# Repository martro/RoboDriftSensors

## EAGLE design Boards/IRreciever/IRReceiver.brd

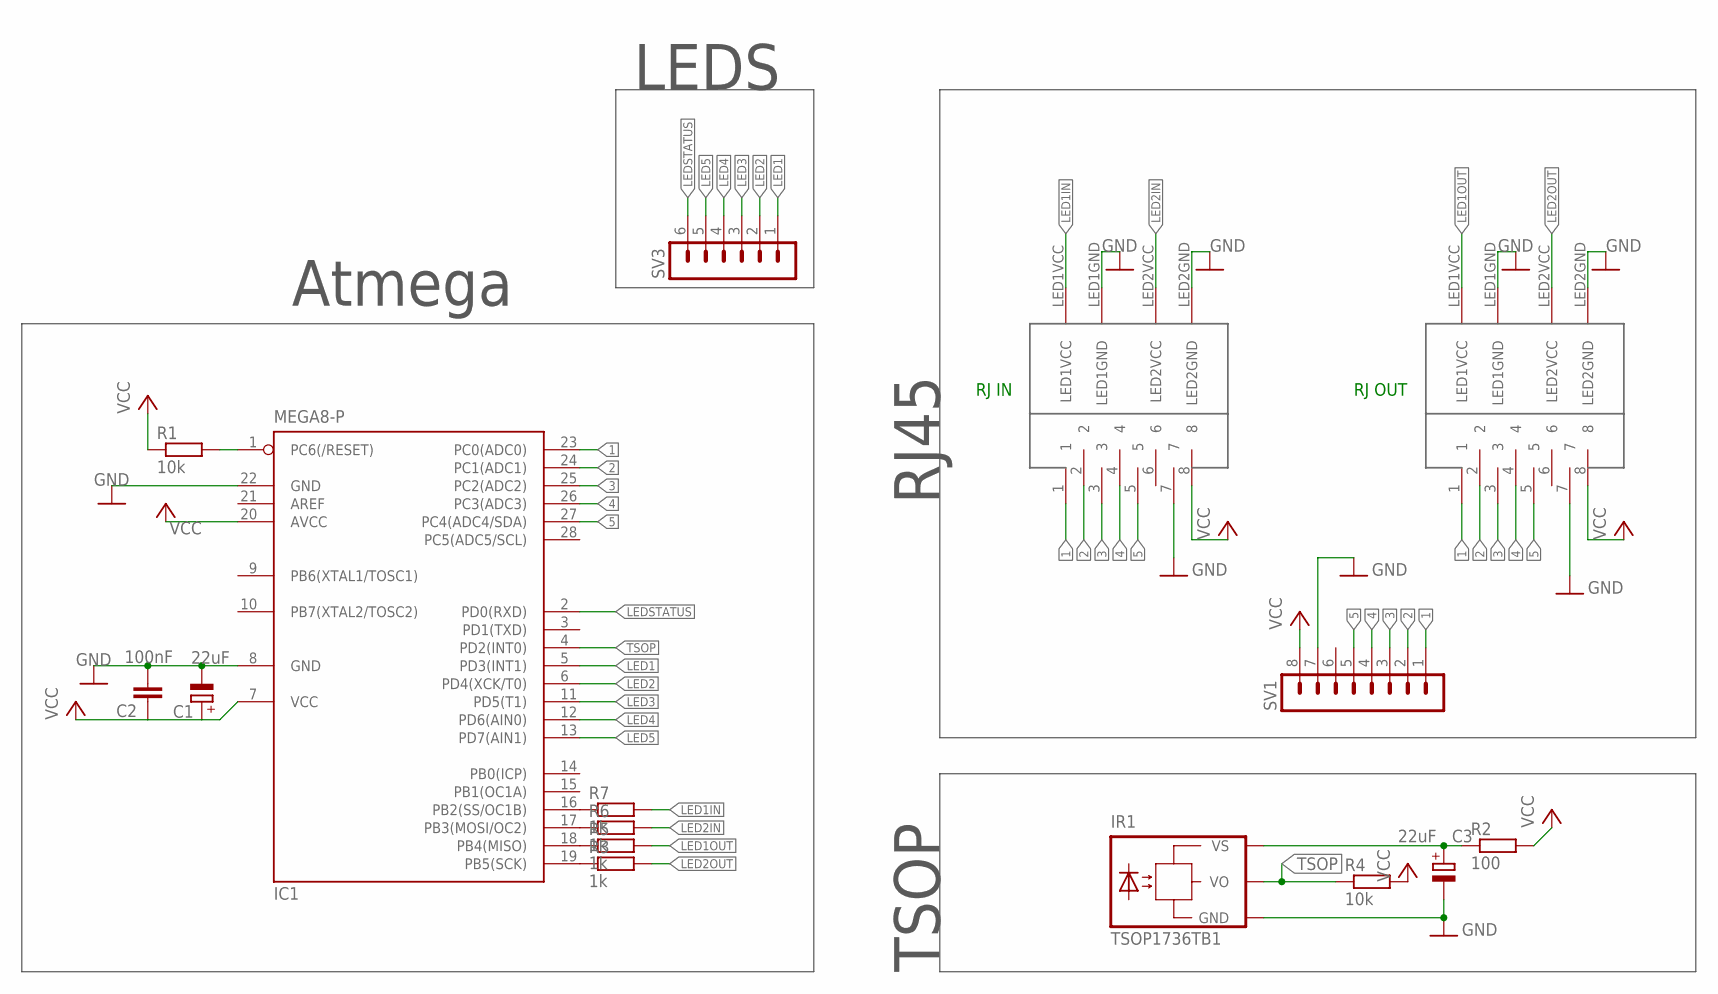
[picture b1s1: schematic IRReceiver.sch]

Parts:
C1, C3: 22uF; E5-5
C2: 100nF; C0805
IC1: MEGA8-P; DIL28-3
IR1: TSOP1736TB1; TSOP17_TB1
R1, R4: 10k; R0805
R2: 100; R0805
R3, R5, R6, R7: 1k; R0805
RJIN, RJIN1: 8P8CLED
SV1: MA08-1
SV3: MA06-1

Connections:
1: IC1.23 (PC0(ADC0)), RJIN.1, RJIN1.1, SV1.1
2: IC1.24 (PC1(ADC1)), RJIN.2, RJIN1.2, SV1.2
3: IC1.25 (PC2(ADC2)), RJIN.3, RJIN1.3, SV1.3
4: IC1.26 (PC3(ADC3)), RJIN.4, RJIN1.4, SV1.4
5: IC1.27 (PC4(ADC4/SDA)), RJIN.5, RJIN1.5, SV1.5
GND: C1.-, C2.2, C3.-, IC1.8 (GND), IC1.22 (GND), IR1.GND, RJIN.7, RJIN.LED1GND, RJIN.LED2GND, RJIN1.7, RJIN1.LED1GND, RJIN1.LED2GND, SV1.7
LED1: IC1.5 (PD3(INT1)), SV3.1
LED1IN: R7.2, RJIN.LED1VCC
LED1OUT: R5.2, RJIN1.LED1VCC
LED2: IC1.6 (PD4(XCK/T0)), SV3.2
LED2IN: R6.2, RJIN.LED2VCC
LED2OUT: R3.2, RJIN1.LED2VCC
LED3: IC1.11 (PD5(T1)), SV3.3
LED4: IC1.12 (PD6(AIN0)), SV3.4
LED5: IC1.13 (PD7(AIN1)), SV3.5
LEDSTATUS: IC1.2 (PD0(RXD)), SV3.6
unnamed: C3.+, IR1.VS, R2.1
unnamed: IC1.1 (PC6(/RESET)), R1.2
unnamed: IC1.19 (PB5(SCK)), R3.1
unnamed: IC1.18 (PB4(MISO)), R5.1
unnamed: IC1.17 (PB3(MOSI/OC2)), R6.1
unnamed: IC1.16 (PB2(SS/OC1B)), R7.1
TSOP: IC1.4 (PD2(INT0)), IR1.VO, R4.1
VCC: C1.+, C2.1, IC1.7 (VCC), IC1.20 (AVCC), R1.1, R2.2, R4.2, RJIN.8, RJIN1.8, SV1.8

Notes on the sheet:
Atmega
RJ IN
RJ OUT
LEDS
TSOP
RJ45

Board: 2 copper layers, 16 parts (0 on the bottom side), 24 nets, no tracks yet.

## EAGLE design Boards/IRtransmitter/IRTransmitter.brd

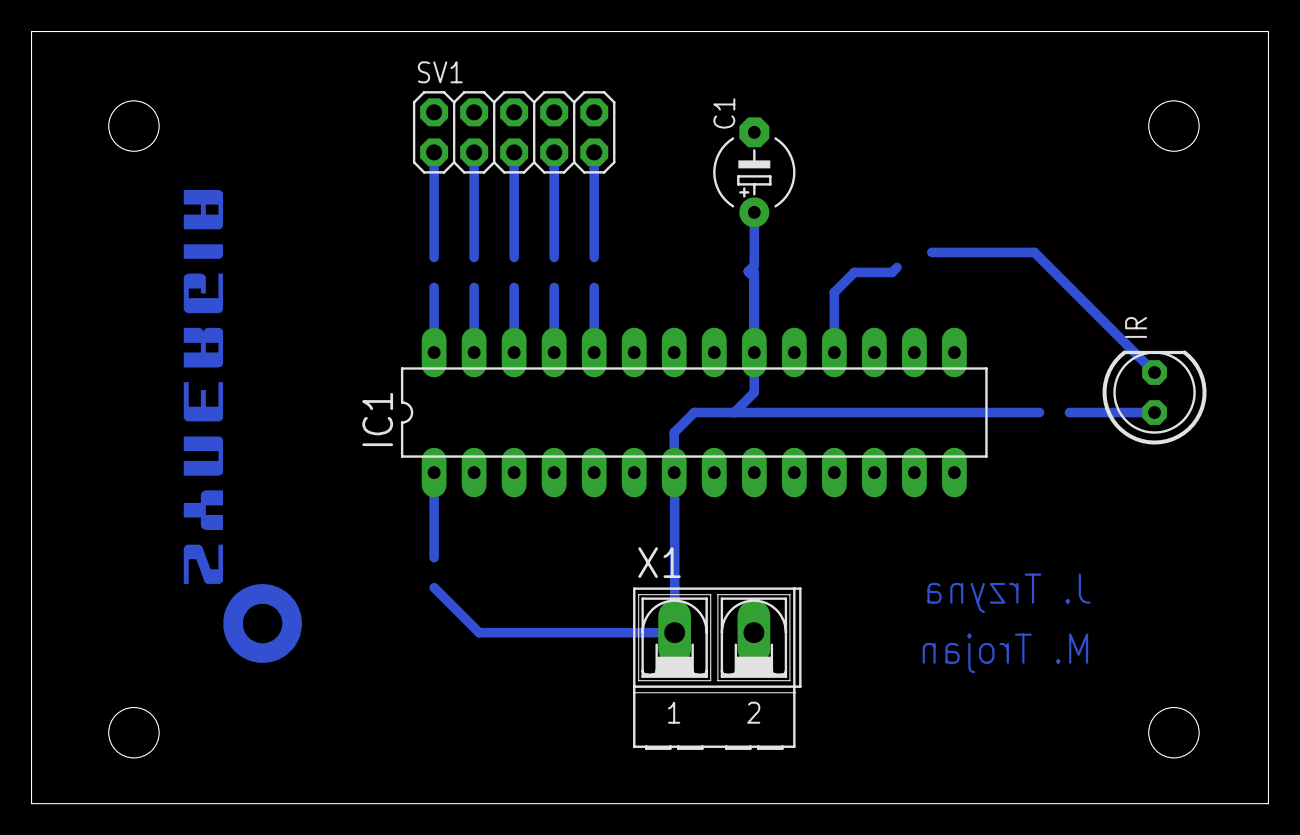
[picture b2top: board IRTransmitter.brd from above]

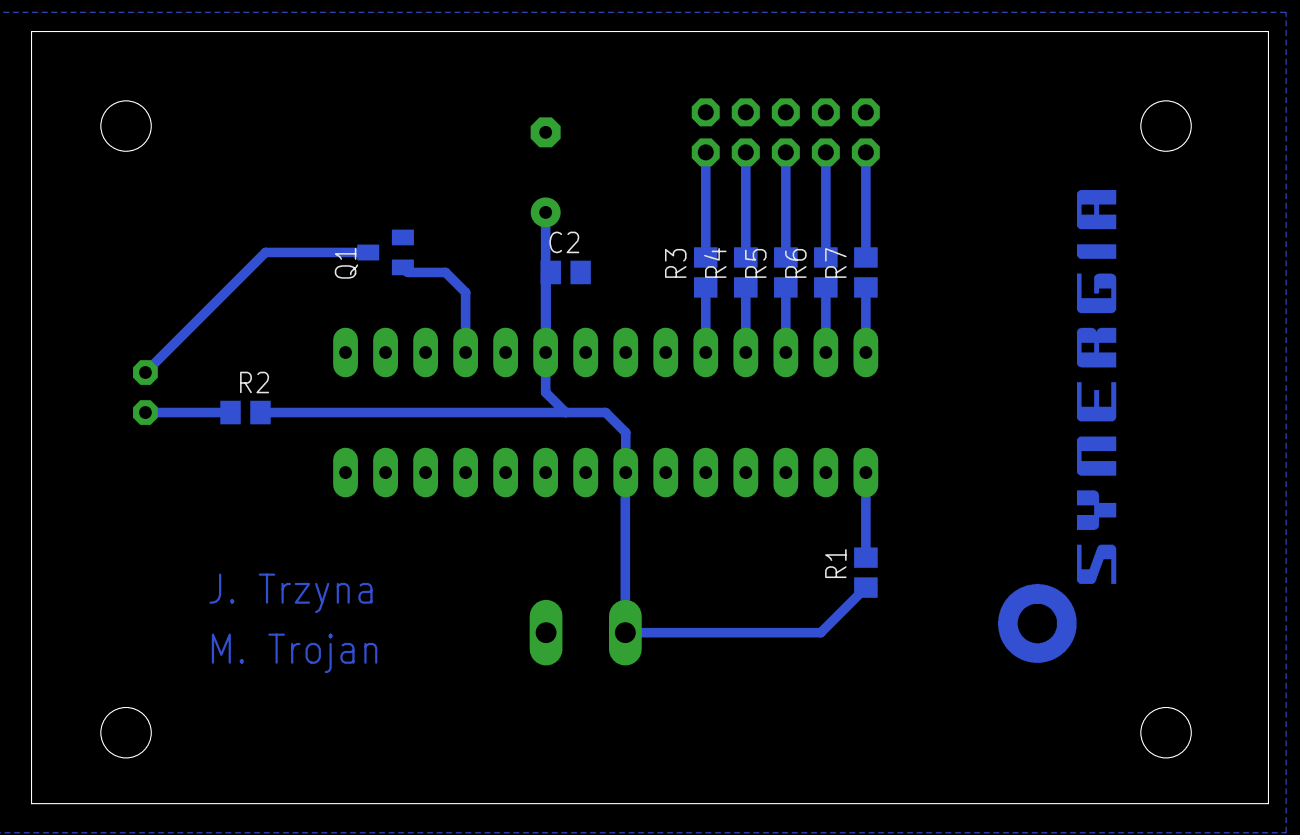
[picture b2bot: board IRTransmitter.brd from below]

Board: 2 copper layers, 78.5 x 49.0 mm, 15 parts (10 on the bottom side), 16 nets.

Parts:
C1: 22uF; E5-5
C2: 100nF; C0805
IC1: MEGA8-P; DIL28-3
IR: LED5MM
Q1: BSS138; SOT23
R1: 10k; R0805
R2: 150; R0805
R3, R4, R5, R6, R7: 1k; R0805
SV1: 2X05
U$1: SYNERGIA_30MM
X1: AK500/2-H

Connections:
GND: C1.-, C2.2, IC1.8, IC1.22, Q1.2, SV1.2, SV1.4, SV1.6, SV1.8, SV1.10, X1.2
LED1: R3.2, SV1.9
LED2: R4.2, SV1.7
LED3: R5.2, SV1.5
LED4: R6.2, SV1.3
LED5: R7.2, SV1.1
unnamed: IR.A, R2.1
unnamed: IC1.1, R1.2
unnamed: IR.K, Q1.3
unnamed: IC1.18, Q1.1
unnamed: IC1.24, R3.1
unnamed: IC1.25, R4.1
unnamed: IC1.26, R5.1
unnamed: IC1.27, R6.1
unnamed: IC1.28, R7.1
VCC: C1.+, C2.1, IC1.7, IC1.20, R1.1, R2.2, X1.1

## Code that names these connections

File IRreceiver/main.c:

#define F_CPU 8000000UL
#define __DELAY_BACKWARD_COMPATIBLE__
#include <util/delay.h>
#include <avr/interrupt.h>

#define YES 1
#define NO 0

#define SYGNAL PD1
#define TSOP PD2

#define LED1IN  PB2
#define LED2IN  PB3
#define LED1OUT PB4
#define LED2OUT PB5

#define LEDSTATUS PD0
#define LED1 PD3
#define LED2 PD4
#define LED3 PD5
#define LED4 PD6
#define LED5 PD7

#define IN1 PC0
#define IN2 PC1
#define IN3 PC2
#define IN4 PC3
#define IN5 PC4

volatile uint8_t LogicalChange;
void set_Diodes_OFF()
{
    PORTD &= ~(1<<LED1)&~(1<<LED2)&~(1<<LED3)&~(1<<LED4)&~(1<<LED5);
}
void set_Diode()
{
    set_Diodes_OFF();
    PORTD |= 1<<LED1;
    _delay_ms(200);
    set_Diodes_OFF();
    PORTD |= 1<<LED2;
    _delay_ms(200);
    set_Diodes_OFF();
    PORTD |= 1<<LED3;
    _delay_ms(200);
    set_Diodes_OFF();
    PORTD |= 1<<LED4;
    _delay_ms(200);
    set_Diodes_OFF();
    PORTD |= 1<<LED5;
    _delay_ms(200);
    set_Diodes_OFF();

    PORTD |= 1<<LED1;
}

void init_PORT()
{
    DDRD = 255;
    DDRD &= ~(1<<TSOP);

    DDRB |= (1<<LED1IN)|(1<<LED2IN)|(1<<LED1OUT)|(1<<LED2OUT); //wyjscja na ledy przy RJ45
    DDRD |= (1<<LED1)|(1<<LED2)|(1<<LED3)|(1<<LED4)|(1<<LED5); //wujscia na ledy

    set_Diode();

    DDRC |= (1<<IN1); //wyjscie na czujke aktulaną

}

void init_TIMER0()
{
    TCCR0 |= (1<<CS02)|(0<<CS01)|(0<<CS00); //preskaler 256 -> rozdzielczość 8ms
    TIMSK |= (1<<TOIE0); //ovf int enable
}

void init_INTERRUPT0()
{
    MCUCR |= (0<<ISC01)|(1<<ISC00); // any logical change genereates interrupt
    GICR |= (1<<INT0);
}

ISR(INT0_vect)
{
    LogicalChange++;
}

ISR(TIMER0_OVF_vect)
{
    if(LogicalChange == 0)
    {
        PORTC |= (1<<IN1);
        PORTD &= ~(1<<LEDSTATUS);
    }
    else
    {
         PORTC &= ~(1<<IN1);
         PORTD |= (1<<LEDSTATUS);
    }
    LogicalChange = 0;
}

int main(void)
{
    init_PORT();
    init_TIMER0();
    init_INTERRUPT0();

    LogicalChange = 1;
    sei();

    while(1)
    {

        PORTB = (1<<LED1IN);
        _delay_ms(200);
        PORTB = (1<<LED1OUT);
        _delay_ms(200);
        PORTB = (1<<LED2IN);
        _delay_ms(200);
        PORTB = (1<<LED2OUT);
        _delay_ms(200);

    }
}

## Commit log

2014-05-26 FIrst commit UML Diagram
2014-05-26 readme added
2014-05-26 first class - sensors
2014-05-26 ream, leader, device classes
2014-05-26 reupload
2014-05-28 dodanie projektu QT
2014-05-28 qt admin window
2014-05-28 uml diagram
2014-05-28 program removed, updated UML
2014-05-28 qt program-template of new race window
2014-05-29 window stats added
2014-05-29 window add team added
2014-05-31 tworzenie wzorcow dla QWidgetow. Dziala dodawanie i usuwanie, pod warunkiem ze wlacza sie jeden element. Dodaje sie na 1 a usuwa na 2, 3 nic nie robi. Teraz trzeba na podstawie tego zrobic mainwindow.
2014-05-31 including widgets to mainwindow works in the example youtube file
2014-05-31 this is to test dialog box
2014-05-31 class team, windowAdmin created
2014-05-31 ui of WindowAdmin and WindowAddTeam
2014-05-31 dialog box, doesnt work
2014-06-01 window add leader added, and fixed some bugs
2014-06-01 added image
2014-06-01 resize add leader
2014-06-01 combobox using connection between signal from edit team and slot at addteam
2014-06-01 communication between windowadmin and windowaddteam doesnt work
2014-06-02 fixed warnings
2014-06-02 vector doesnt disappear
2014-06-02 deleting unused window ( WindowEditTeam)
2014-06-02 images added
2014-06-02 team name indicator added
2014-06-02 fatal error repaired
2014-06-04 check team name indicator added
2014-06-04 WindowEditTeam includes indicator good/bad name and can disable save button in window add team
2014-06-04 great update: simplified code, adding and editing team name works
2014-06-05 adding and editting team name works properly
2014-06-05 little safety improvment(disable all buttons if combobox not activated)
2014-06-05 communication with avr works fine
2014-06-05 comunication gui, first led indicators
2014-06-05 adding leader name and surname
2014-06-05 adding all leader parameters
2014-06-05 displaying data from atmega (binary to QString
2014-06-05 avr bug fixed
2014-06-05 adding members, editting doesn.t work
2014-06-05 leds sensor indicator works fine
2014-06-05 editting members of team works fantastic
2014-06-05 trying to delete dictionary
2014-06-05 delate rest of unused files
2014-06-06 eclipse works
2014-06-06 deleted RDSystem/PC
2014-06-06 removed AVR folder
2014-06-06 timer test branch edit
2014-06-06 timer works in test mode
2014-06-06 countdown works in TimerTest directory
2014-06-06 race window added
2014-06-06 adding cars
2014-06-06 deleting cars
2014-06-06 minor bug fixed(adding/editing cars&members)
2014-06-06 added timer and usart to race project
2014-06-06 MainUserWindow added. messy at this moment
2014-06-06 window racemain added
2014-06-06 fatal error(that unexpectedly occured) removed ...probably
2014-06-06 fatal bug discovered and fixed
2014-06-07 prepere to connect racemain with user main
2014-06-07 bug:Qap<plication no such file or directory> fixed
2014-06-07 button connection between racemain adn usermain works fine
2014-06-07 connection button works and emits signal
2014-06-07 Saving teams to XML file
2014-06-07 setting cars ID fixed
2014-06-07 reading from XML file and adding everything to list of teams
2014-06-07 FATAL ERROR FOUND AND FIXED!!! serial must not be a global variable!
2014-06-07 windowracemain starts working
2014-06-07 lamp added. cant resize it
2014-06-07 cars ID functionality added
2014-06-08 start lights exist
2014-06-08 lamps modes added
2014-06-08 last commit before merging
2014-06-08 xml file saving to current dictionary
2014-06-08 start lights are visible again after merging
2014-06-09 info about countdown passed to raceuser
2014-06-09 start lights countdwon works
2014-06-09 adding connection between windowAdmin and WindowRaceMain
2014-06-09 deleting unused files(previous windowRace)
2014-06-09 fixing minor errors (startlights) after merge
2014-06-09 if race clicked, doesnt make a new race window
2014-06-09 Empty window stats added
2014-06-09 conection windowRace gets info about teams and results
2014-06-09 time measure
2014-06-09 falstart option added
2014-06-09 Passing bestTIme from WindowAdmin to WindowRace
2014-06-09 function display time added
2014-06-10 dangerous fail with reading cars categories fixed
2014-06-10 sorting cars and teams
2014-06-10 cars ID added to comboBoxID in WindowRace (unsorted)
2014-06-10 sorting cars IDs in comboBoxID in WindowRace
2014-06-11 new resources added - sounds
2014-06-11 beep sounds merged
2014-06-11 function displaying times on labels
2014-06-11 commit before chcnging led data to class
2014-06-11 connected successfuly
2014-06-11 sending class to userracemain works fine
2014-06-11 Timer and Info about car displayd on windowUserRace
2014-06-11 Falstart/receiving data from every sensor fixed
2014-06-11 race ends after expire of chosen number of laps
2014-06-11 nmany laps allowed
2014-06-11 falstart fixed, clear button works
2014-06-12 checking falstart disabled to avoid lag
2014-06-20 dont have to close the program to take another race
2014-06-20 WindowRace (admin) displays team/car name
2014-06-20 Falstart fixed
2014-06-20 number of laps is the same for each category
2014-06-20 small bug with starting race fixed, saving results to xml finction added(doesnt work as it should
2014-06-22 saving best time of category, now we challenge each other !
2014-06-22 reading best time from xml
2014-06-22 gathering info from xml about category <MO> works correctly
2014-06-22 XML file with results fully readable
2014-06-23 the same time displayed in WIndowUser and WIndowAdmin, without this tiny diffrence (abot 2ms)
2014-06-23 gererating pdf from tex file: button stats->generate
2014-06-23 memory leakage found and fixed (pixmap of lamps)
2014-06-24 indicato"current position" added
2014-06-24 avr project added
2014-06-24 merge. added xml time structure changed
2014-06-24 displaying current position during the race, category: MO only
2014-06-25 checkig position during every category, hiding diffrence time after each lap
2014-06-25 making pdf file with summary table of all cars/teams
2014-06-25 making c correct number of tables (PDF file with stats&results)
2014-06-26 PDF contain: times of sectors in category RC, summary Time of race
2014-06-27 PDF with results looks fine
2014-06-28 IR Diode transmitter - receiver doesnt fall asleep, distance above 3m, 2 red glass covers, min time reaction 4ms
2014-06-30 WIndowUserStats with (no shit Sherlock!) statistics visible for users added
2014-06-30 displaying stats of all cars, setting car position after reading results from XML
2014-06-30 warning about comparison between signed and unsigned int fixed
2014-06-30 changed way of dispalying stats
2014-06-30 unused files deleted
2014-07-01 shcematic and board of IR transmitter
2014-07-01 schematic of IR receiver
2014-07-01 added avr project file
2014-07-01 new branch
2014-07-01 branch
2014-07-02 connection with PC works on new main board
2014-07-02 start lights on main board work
2014-07-04 version to merge
2014-07-04 merge
